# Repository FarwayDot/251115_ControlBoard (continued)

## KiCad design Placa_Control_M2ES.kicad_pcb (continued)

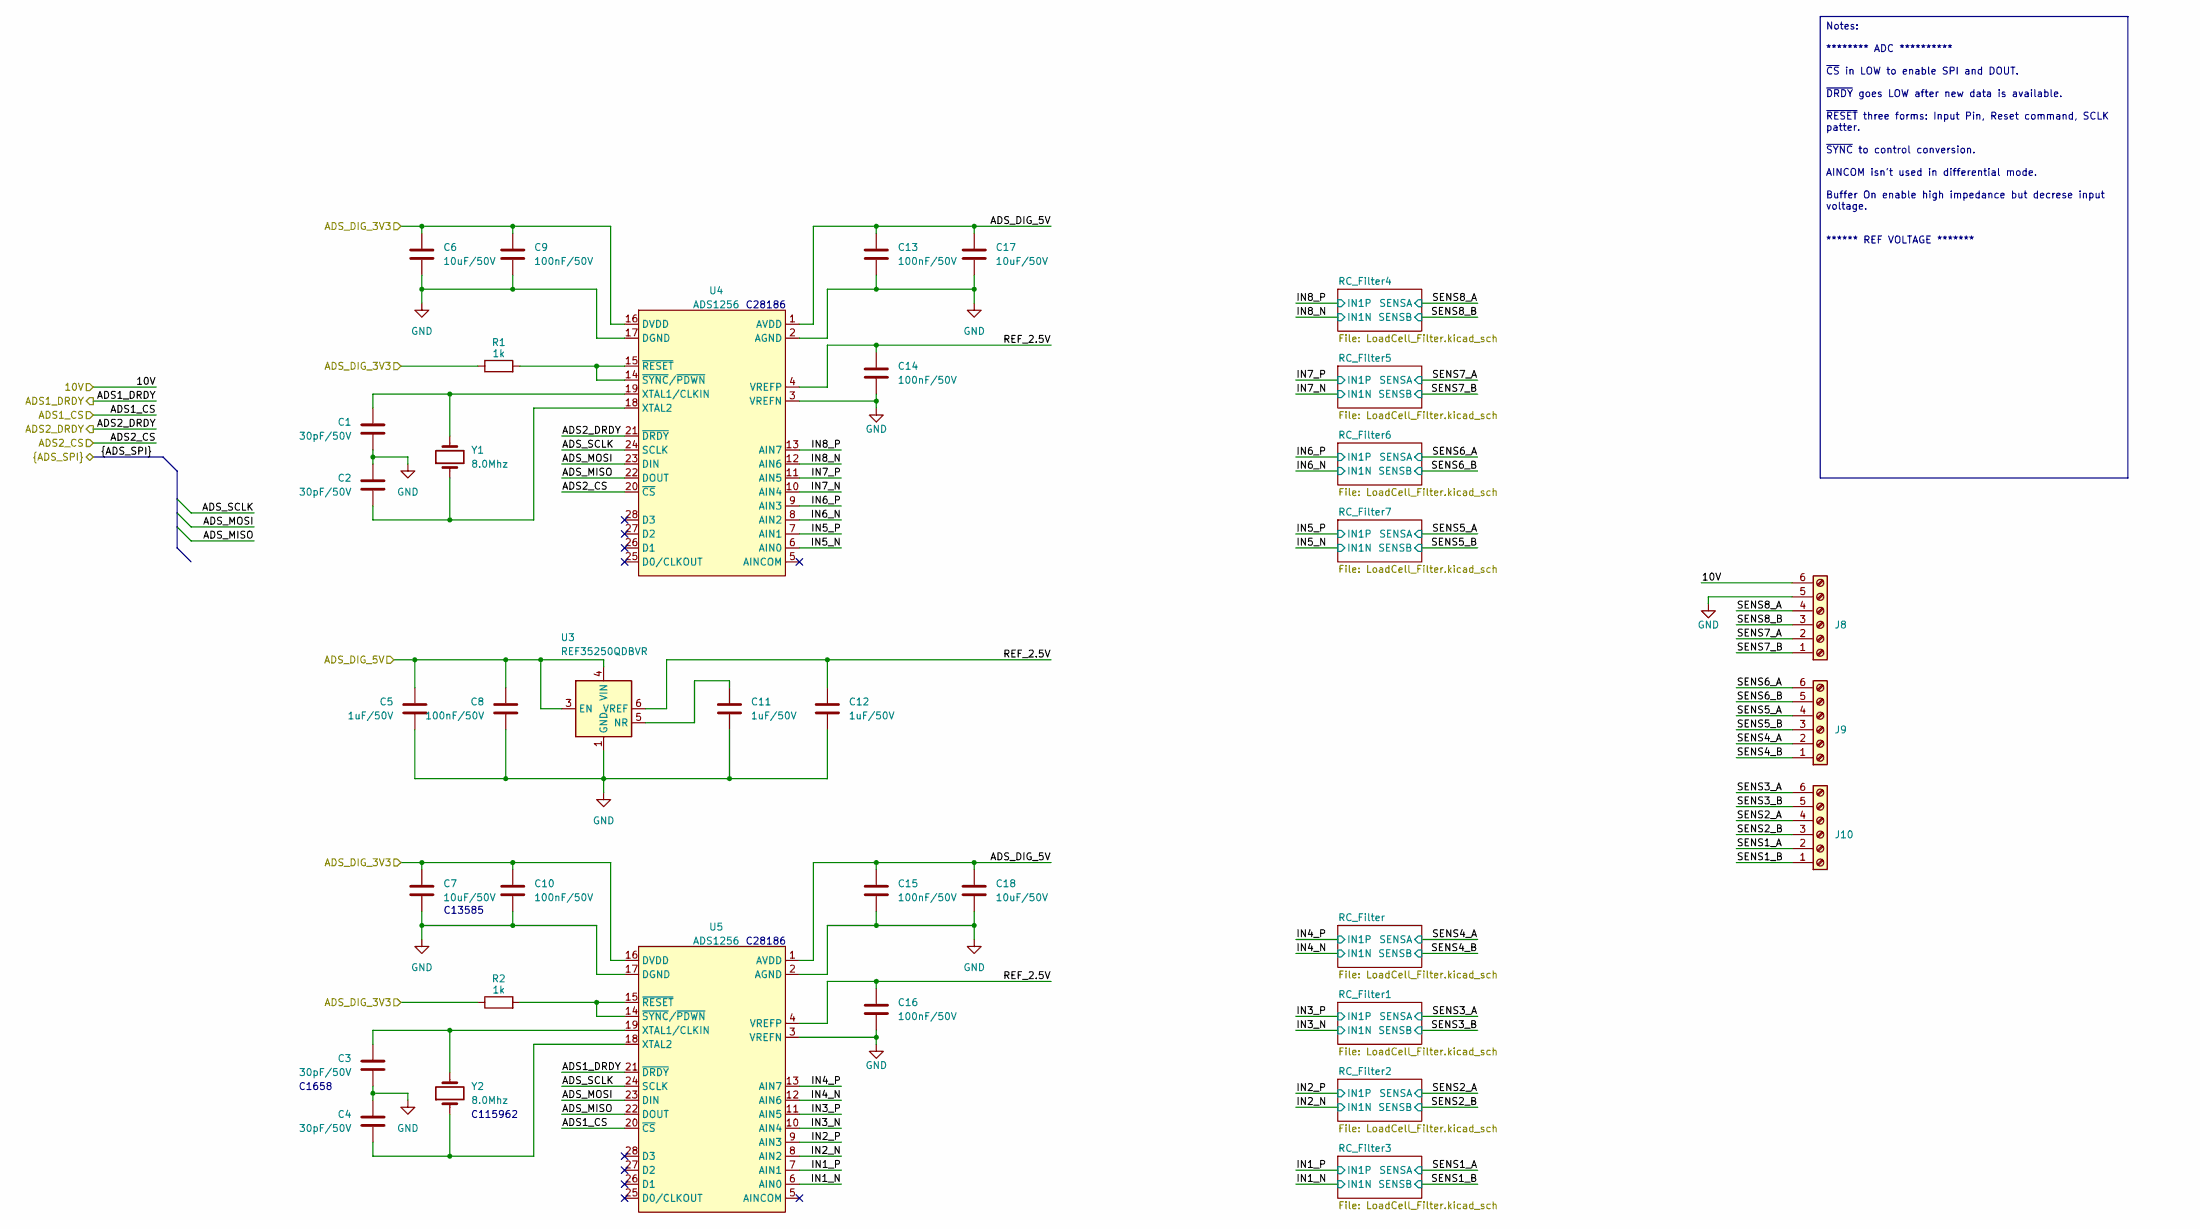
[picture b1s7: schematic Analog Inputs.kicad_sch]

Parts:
C1, C2, C3, C4: 30pF/50V; C_0603_1608Metric
C5, C11, C12: 1uF/50V; C_0805_2012Metric
C6, C7, C17, C18: 10uF/50V; C_1206_3216Metric
C8, C9, C10, C13, C14, C15, C16: 100nF/50V; C_0603_1608Metric
J8, J9, J10: Screw_Terminal_01x06; 15EDGVC_6P_3.81mm_Male-Vert_Degson
R1, R2: 1k; R_0603_1608Metric
U3: REF35250QDBVR; SOT-23-6
U4, U5: ADS1256; SSOP-28_5.3x10.2mm_P0.65mm
Y1, Y2: 8.0Mhz; Crystal_SMD_5032-2Pin_5.0x3.2mm

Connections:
/5V: C5.1, C8.1, C13.1, C15.1, C17.1, C18.1, U3.3 (EN), U3.4 (VIN), U4.1 (AVDD), U5.1 (AVDD); also elsewhere on the board
/10V: J8.6; also elsewhere on the board
/Analog Inputs/ADS1_CS: U5.20 (~CS); also elsewhere on the board
/Analog Inputs/ADS1_DRDY: U5.21 (~DRDY); also elsewhere on the board
/Analog Inputs/ADS2_CS: U4.20 (~CS); also elsewhere on the board
/Analog Inputs/ADS2_DRDY: U4.21 (~DRDY); also elsewhere on the board
/Analog Inputs/ADS_MISO: U4.22 (DOUT), U5.22 (DOUT); also elsewhere on the board
/Analog Inputs/ADS_MOSI: U4.23 (DIN), U5.23 (DIN); also elsewhere on the board
/Analog Inputs/ADS_SCLK: U4.24 (SCLK), U5.24 (SCLK); also elsewhere on the board
/Analog Inputs/IN1_N: U5.6 (AIN0); also elsewhere on the board
/Analog Inputs/IN2_N: U5.8 (AIN2); also elsewhere on the board
/Analog Inputs/IN2_P: U5.9 (AIN3); also elsewhere on the board
/Analog Inputs/IN3_N: U5.10 (AIN4); also elsewhere on the board
/Analog Inputs/IN3_P: U5.11 (AIN5); also elsewhere on the board
/Analog Inputs/IN4_N: U5.12 (AIN6); also elsewhere on the board
/Analog Inputs/IN4_P: U5.13 (AIN7); also elsewhere on the board
/Analog Inputs/IN5_N: U4.6 (AIN0); also elsewhere on the board
/Analog Inputs/IN5_P: U4.7 (AIN1); also elsewhere on the board
/Analog Inputs/IN6_N: U4.8 (AIN2); also elsewhere on the board
/Analog Inputs/IN6_P: U4.9 (AIN3); also elsewhere on the board
/Analog Inputs/IN7_N: U4.10 (AIN4); also elsewhere on the board
/Analog Inputs/IN7_P: U4.11 (AIN5); also elsewhere on the board
/Analog Inputs/IN8_N: U4.12 (AIN6); also elsewhere on the board
/Analog Inputs/IN8_P: U4.13 (AIN7); also elsewhere on the board
/Analog Inputs/REF_2.5V: C12.1, C14.1, C16.1, U3.6 (VREF), U4.4 (VREFP), U5.4 (VREFP)
/Analog Inputs/SENS1_A: J10.2; also elsewhere on the board
/Analog Inputs/SENS1_B: J10.1; also elsewhere on the board
/Analog Inputs/SENS2_A: J10.4; also elsewhere on the board
/Analog Inputs/SENS2_B: J10.3; also elsewhere on the board
/Analog Inputs/SENS3_A: J10.6; also elsewhere on the board
/Analog Inputs/SENS3_B: J10.5; also elsewhere on the board
/Analog Inputs/SENS4_A: J9.2; also elsewhere on the board
/Analog Inputs/SENS4_B: J9.1; also elsewhere on the board
/Analog Inputs/SENS5_A: J9.4; also elsewhere on the board
/Analog Inputs/SENS5_B: J9.3; also elsewhere on the board
/Analog Inputs/SENS6_A: J9.6; also elsewhere on the board
/Analog Inputs/SENS6_B: J9.5; also elsewhere on the board
/Analog Inputs/SENS7_A: J8.2; also elsewhere on the board
/Analog Inputs/SENS7_B: J8.1; also elsewhere on the board
/Analog Inputs/SENS8_A: J8.4; also elsewhere on the board
/Analog Inputs/SENS8_B: J8.3; also elsewhere on the board
GND: C1.2, C2.1, C3.2, C4.1, C5.2, C6.2, C7.2, C8.2, C9.2, C10.2, C11.2, C12.2, C13.2, C14.2, C15.2, C16.2, C17.2, C18.2, J8.5, U3.1 (GND), U3.2 (GND), U4.2 (AGND), U4.3 (VREFN), U4.17 (DGND), U5.2 (AGND), U5.3 (VREFN), U5.17 (DGND); also elsewhere on the board
unnamed: C11.1, U3.5 (NR)
unnamed: C1.1, U4.19 (XTAL1/CLKIN), Y1.2
unnamed: C2.2, U4.18 (XTAL2), Y1.1
unnamed: R1.2, U4.14 (~SYNC/~PDWN), U4.15 (~RESET)
unnamed: C3.1, U5.19 (XTAL1/CLKIN), Y2.2
unnamed: C4.2, U5.18 (XTAL2), Y2.1
unnamed: R2.2, U5.14 (~SYNC/~PDWN), U5.15 (~RESET)

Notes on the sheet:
C13585
C115962
C1658
C28186
Notes: ******** ADC ********** ~{CS} in LOW to enable SPI and DOUT. ~{DRDY} goes LOW after new data is available. ~{RESET} three forms: Input Pin, Reset command, SCLK patter. ~{SYNC} to control conversion. AINCOM isn't used in differential mode. Buffer On enable high impedance but decrese input vol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

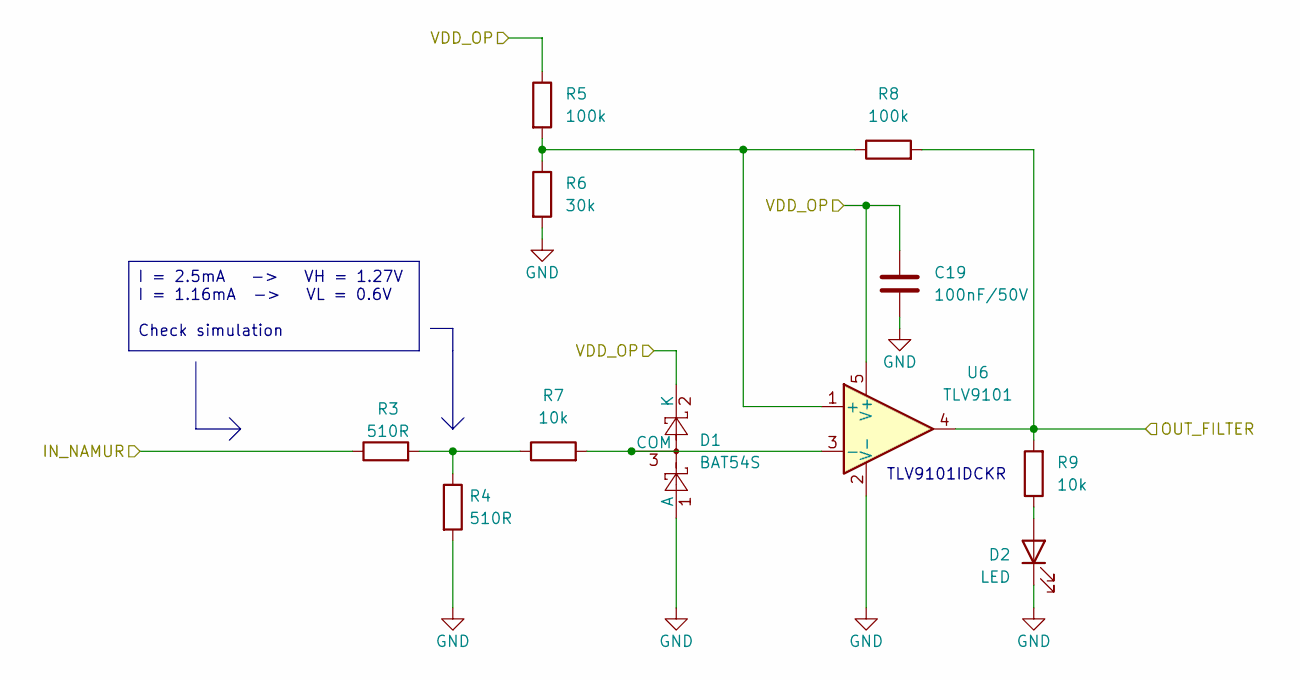
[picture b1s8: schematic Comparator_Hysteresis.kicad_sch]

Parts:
C19: 100nF/50V; C_0603_1608Metric
D1: BAT54S; SOT-23
D2: LED; LED_0805_2012Metric
R3, R4: 510R; R_0603_1608Metric
R5, R8: 100k; R_0603_1608Metric
R6: 30k; R_0603_1608Metric
R7, R9: 10k; R_0603_1608Metric
U6: TLV9101; SC70-5_TexasInstruments

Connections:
/Digital Inputs/DIG_2: R8.2, R9.2, U6.4; also elsewhere on the board
/Digital Inputs/NAMUR_2: R3.1; also elsewhere on the board
GND: C19.2, D1.1 (A), D2.1 (K), R4.2, R6.2, U6.2 (V-); also elsewhere on the board
unnamed: D1.3 (COM), R7.2, U6.3 (-)
unnamed: D2.2 (A), R9.1
unnamed: R3.2, R4.1, R7.1
unnamed: R5.2, R6.1, R8.1, U6.1 (+)

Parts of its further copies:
C66, C67, C68, C69, C70, C71, C72, C73: 100nF/50V; C_0603_1608Metric
D3, D5, D7, D9, D11, D13, D15, D17: BAT54S; SOT-23
D4, D6, D8, D10, D12, D14, D16, D18: LED; LED_0805_2012Metric
R60, R61, R67, R68, R74, R75, R81, R82, R88, R89, R95, R96, R102, R103, R109, R110: 510R; R_0603_1608Metric
R62, R65, R69, R72, R76, R79, R83, R86, R90, R93, R97, R100, R104, R107, R111, R114: 100k; R_0603_1608Metric
R63, R70, R77, R84, R91, R98, R105, R112: 30k; R_0603_1608Metric
R64, R66, R71, R73, R78, R80, R85, R87, R92, R94, R99, R101, R106, R108, R113, R115: 10k; R_0603_1608Metric
U14, U15, U16, U17, U18, U19, U20, U21: TLV9101; SC70-5_TexasInstruments

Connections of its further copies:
/Digital Inputs/DIG_1: R65.2, R66.2, U14.4; also elsewhere on the board
/Digital Inputs/DIG_3: R72.2, R73.2, U15.4; also elsewhere on the board
/Digital Inputs/DIG_4: R79.2, R80.2, U16.4; also elsewhere on the board
/Digital Inputs/DIG_5: R86.2, R87.2, U17.4; also elsewhere on the board
/Digital Inputs/DIG_6: R93.2, R94.2, U18.4; also elsewhere on the board
/Digital Inputs/DIG_7: R100.2, R101.2, U19.4; also elsewhere on the board
/Digital Inputs/DIG_8: R107.2, R108.2, U20.4; also elsewhere on the board
/Digital Inputs/DIG_9: R114.2, R115.2, U21.4; also elsewhere on the board
/Digital Inputs/NAMUR_1: R60.1; also elsewhere on the board
/Digital Inputs/NAMUR_3: R67.1; also elsewhere on the board
/Digital Inputs/NAMUR_4: R74.1; also elsewhere on the board
/Digital Inputs/NAMUR_5: R81.1; also elsewhere on the board
/Digital Inputs/NAMUR_6: R88.1; also elsewhere on the board
/Digital Inputs/NAMUR_7: R95.1; also elsewhere on the board
/Digital Inputs/NAMUR_8: R102.1; also elsewhere on the board
/Digital Inputs/NAMUR_9: R109.1; also elsewhere on the board
GND: C66.2, C67.2, C68.2, C69.2, C70.2, C71.2, C72.2, C73.2, D3.1 (A), D4.1 (K), D5.1 (A), D6.1 (K), D7.1 (A), D8.1 (K), D9.1 (A), D10.1 (K), D11.1 (A), D12.1 (K), D13.1 (A), D14.1 (K), D15.1 (A), D16.1 (K), D17.1 (A), D18.1 (K), R61.2, R63.2, R68.2, R70.2, R75.2, R77.2, R82.2, R84.2, R89.2, R91.2, R96.2, R98.2, R103.2, R105.2, R110.2, R112.2, U14.2 (V-), U15.2 (V-), U16.2 (V-), U17.2 (V-), U18.2 (V-), U19.2 (V-), U20.2 (V-), U21.2 (V-); also elsewhere on the board
unnamed: D3.3 (COM), R64.2, U14.3 (-)
unnamed: D4.2 (A), R66.1
unnamed: D5.3 (COM), R71.2, U15.3 (-)
unnamed: D6.2 (A), R73.1
unnamed: D7.3 (COM), R78.2, U16.3 (-)
unnamed: D8.2 (A), R80.1
unnamed: D9.3 (COM), R85.2, U17.3 (-)
unnamed: D10.2 (A), R87.1
unnamed: D11.3 (COM), R92.2, U18.3 (-)
unnamed: D12.2 (A), R94.1
unnamed: D13.3 (COM), R99.2, U19.3 (-)
unnamed: D14.2 (A), R101.1
unnamed: D15.3 (COM), R106.2, U20.3 (-)
unnamed: D16.2 (A), R108.1
unnamed: D17.3 (COM), R113.2, U21.3 (-)
unnamed: D18.2 (A), R115.1
unnamed: R60.2, R61.1, R64.1
unnamed: R67.2, R68.1, R71.1
unnamed: R74.2, R75.1, R78.1
unnamed: R81.2, R82.1, R85.1
unnamed: R88.2, R89.1, R92.1
unnamed: R95.2, R96.1, R99.1
unnamed: R102.2, R103.1, R106.1
unnamed: R109.2, R110.1, R113.1
unnamed: R62.2, R63.1, R65.1, U14.1 (+)
unnamed: R69.2, R70.1, R72.1, U15.1 (+)
unnamed: R76.2, R77.1, R79.1, U16.1 (+)
unnamed: R83.2, R84.1, R86.1, U17.1 (+)
unnamed: R90.2, R91.1, R93.1, U18.1 (+)
unnamed: R97.2, R98.1, R100.1, U19.1 (+)
unnamed: R104.2, R105.1, R107.1, U20.1 (+)
unnamed: R111.2, R112.1, R114.1, U21.1 (+)

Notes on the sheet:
TLV9101IDCKR
I = 2.5mA -> VH = 1.27V I = 1.16mA -> VL = 0.6V Check simulation

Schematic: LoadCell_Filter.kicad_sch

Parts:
C31: 10nF/50V; C_0603_1608Metric
C32, C33: 1nF/50V; C_0603_1608Metric
R10, R11, R12, R13: 10k; R_0603_1608Metric

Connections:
/Analog Inputs/IN4_N: C31.2, C33.2, R11.2, R13.1; also elsewhere on the board
/Analog Inputs/IN4_P: C31.1, C32.1, R10.1, R12.1; also elsewhere on the board
/Analog Inputs/SENS4_A: R12.2; also elsewhere on the board
/Analog Inputs/SENS4_B: R13.2; also elsewhere on the board
GND: C32.2, C33.1, R10.2, R11.1; also elsewhere on the board

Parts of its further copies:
C34, C37, C40, C43, C46, C49, C63: 10nF/50V; C_0603_1608Metric
C35, C36, C38, C39, C41, C42, C44, C45, C47, C48, C50, C51, C64, C65: 1nF/50V; C_0603_1608Metric
R14, R15, R16, R17, R18, R19, R20, R21, R22, R23, R24, R25, R26, R27, R28, R29, R30, R31, R32, R33, R34, R35, R36, R37, R56, R57, R58, R59: 10k; R_0603_1608Metric

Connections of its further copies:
/Analog Inputs/IN1_N: C40.2, C42.2, R23.2, R25.1; also elsewhere on the board
/Analog Inputs/IN2_N: C34.2, C36.2, R15.2, R17.1; also elsewhere on the board
/Analog Inputs/IN2_P: C34.1, C35.1, R14.1, R16.1; also elsewhere on the board
/Analog Inputs/IN3_N: C37.2, C39.2, R19.2, R21.1; also elsewhere on the board
/Analog Inputs/IN3_P: C37.1, C38.1, R18.1, R20.1; also elsewhere on the board
/Analog Inputs/IN5_N: C63.2, C65.2, R57.2, R59.1; also elsewhere on the board
/Analog Inputs/IN5_P: C63.1, C64.1, R56.1, R58.1; also elsewhere on the board
/Analog Inputs/IN6_N: C49.2, C51.2, R35.2, R37.1; also elsewhere on the board
/Analog Inputs/IN6_P: C49.1, C50.1, R34.1, R36.1; also elsewhere on the board
/Analog Inputs/IN7_N: C46.2, C48.2, R31.2, R33.1; also elsewhere on the board
/Analog Inputs/IN7_P: C46.1, C47.1, R30.1, R32.1; also elsewhere on the board
/Analog Inputs/IN8_N: C43.2, C45.2, R27.2, R29.1; also elsewhere on the board
/Analog Inputs/IN8_P: C43.1, C44.1, R26.1, R28.1; also elsewhere on the board
/Analog Inputs/SENS1_A: R24.2; also elsewhere on the board
/Analog Inputs/SENS1_B: R25.2; also elsewhere on the board
/Analog Inputs/SENS2_A: R16.2; also elsewhere on the board
/Analog Inputs/SENS2_B: R17.2; also elsewhere on the board
/Analog Inputs/SENS3_A: R20.2; also elsewhere on the board
/Analog Inputs/SENS3_B: R21.2; also elsewhere on the board
/Analog Inputs/SENS5_A: R58.2; also elsewhere on the board
/Analog Inputs/SENS5_B: R59.2; also elsewhere on the board
/Analog Inputs/SENS6_A: R36.2; also elsewhere on the board
/Analog Inputs/SENS6_B: R37.2; also elsewhere on the board
/Analog Inputs/SENS7_A: R32.2; also elsewhere on the board
/Analog Inputs/SENS7_B: R33.2; also elsewhere on the board
/Analog Inputs/SENS8_A: R28.2; also elsewhere on the board
/Analog Inputs/SENS8_B: R29.2; also elsewhere on the board
GND: C35.2, C36.1, C38.2, C39.1, C41.2, C42.1, C44.2, C45.1, C47.2, C48.1, C50.2, C51.1, C64.2, C65.1, R14.2, R15.1, R18.2, R19.1, R22.2, R23.1, R26.2, R27.1, R30.2, R31.1, R34.2, R35.1, R56.2, R57.1; also elsewhere on the board

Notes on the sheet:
To ADC
From Sensor
Notes: - Use Precision Resistor - Fc = 1500Hz (simulated)

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
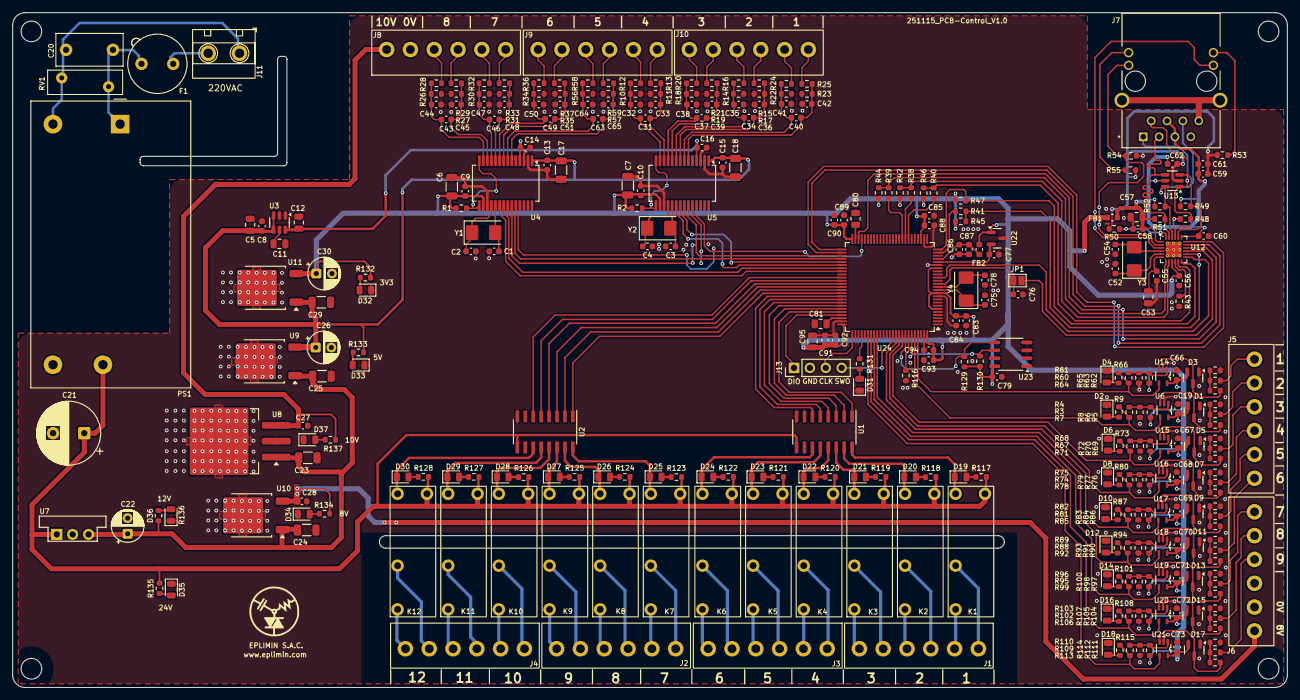
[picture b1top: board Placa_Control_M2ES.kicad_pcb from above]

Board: 2 copper layers, 204.0 x 108.0 mm, 326 parts (0 on the bottom side), 221 nets.

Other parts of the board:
G1: LOGO

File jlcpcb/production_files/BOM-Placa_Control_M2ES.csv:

Comment,Designator,Footprint,LCSC,Quantity
450mR/200mA,"FB1,FB2",L_0603_1608Metric,C1002,2
USBLC6-4SC6,U13,SOT-23-6,C111212,1
25Mhz,Y3,Crystal_SMD_5032-2Pin_5.0x3.2mm,C112569,1
8.0Mhz,"Y1,Y2,Y4",Crystal_SMD_5032-2Pin_5.0x3.2mm,C115962,3
uA7810,U8,TO-263-3_TabPin2,C131966,1
10uF/50V,"C17,C18,C6,C7",C_1206_3216Metric,C13585,4
100nF/50V,"C10,C13,C14,C15,C16,C19,C27,C28,C56,C58,C59,C60,C61,C62,C66,C67,C68,C69,C70,C71,C72,C73,C76,C77,C79,C8,C83,C85,C87,C89,C9,C91,C93",C_0603_1608Metric,C14663,33
24xx256,U23,SO-8_3.9x4.9mm_P1.27mm,C152172,1
LD29150DT33R,U11,TO-252-2,C155674,1
LD29150DT50R,U9,TO-252-2,C157411,1
L78M08CDT-TR,U10,TO-252-2,C158076,1
1nF/50V,"C32,C33,C35,C36,C38,C39,C41,C42,C44,C45,C47,C48,C50,C51,C64,C65",C_0603_1608Metric,C1588,16
30pF/50V,"C1,C2,C3,C4,C52,C54,C75,C78",C_0603_1608Metric,C1658,8
1uF/50V,"C23,C24,C25,C29",C_1206_3216Metric,C1848,4
1k,"R1,R116,R2,R47",R_0603_1608Metric,C21190,4
12k1,R50,R_0603_1608Metric,C22864,1
30k,"R105,R112,R6,R63,R70,R77,R84,R91,R98",R_0603_1608Metric,C22984,9
33R,"R38,R39,R40,R41",R_0603_1608Metric,C23140,4
49R9,"R48,R49,R51,R52",R_0603_1608Metric,C23185,4
5k1,"R131,R132,R133,R134",R_0603_1608Metric,C23186,4
510R,"R102,R103,R109,R110,R3,R4,R60,R61,R67,R68,R74,R75,R81,R82,R88,R89,R95,R96",R_0603_1608Metric,C23193,18
100k,"R100,R104,R107,R111,R114,R5,R62,R65,R69,R72,R76,R79,R8,R83,R86,R90,R93,R97",R_0603_1608Metric,C25803,18
10k,"R10,R101,R106,R108,R11,R113,R115,R117,R118,R119,R12,R120,R121,R122,R123,R124,R125,R126,R127,R128,R13,R135,R136,R137,R14,R15,R16,R17,R18,R19,R20,R21,R22,R23,R24,R25,R26,R27,R28,R29,R30,R31,R32,R33,R34,R35,R36,R37,R42,R43,R44,R45,R46,R53,R54,R55,R56,R57,R58,R59,R64,R66,R7,R71,R73,R78,R80,R85,R87,R9,R92,R94,R99",R_0603_1608Metric,C25804,73
ADS1256,"U4,U5",SSOP-28_5.3x10.2mm_P0.65mm,C28186,2
1uF/50V,"C11,C12,C5,C53,C57",C_0805_2012Metric,C28323,5
STM32F407VGTx,U24,LQFP-100_14x14mm_P0.5mm,C28730,1
2u2F/50V,"C80,C81,C95",C_0805_2012Metric,C377773,3
REF3030,U22,SOT-23,C38423,1
2k2,"R129,R130",R_0603_1608Metric,C4190,2
TLV9101,"U14,U15,U16,U17,U18,U19,U20,U21,U6",SC70-5_TexasInstruments,C4367797,9
10nF/50V,"C31,C34,C37,C40,C43,C46,C49,C55,C63,C84,C86,C88,C90,C92,C94",C_0603_1608Metric,C57112,15
LAN8742A,U12,VQFN-24-1EP_4x4mm_P0.5mm_EP2.5x2.5mm_ThermalVias,C621425,1
REF35250QDBVR,U3,SOT-23-6,C6265005,1
BAT54S,"D1,D11,D13,D15,D17,D3,D5,D7,D9",SOT-23,C7420333,9
ULN2003,"U1,U2",SOIC-16_3.9x9.9mm_P1.27mm,C7512,2
LED,"D10,D12,D14,D16,D18,D19,D2,D20,D21,D22,D23,D24,D25,D26,D27,D28,D29,D30,D31,D32,D33,D34,D35,D36,D37,D4,D6,D8",LED_0805_2012Metric,C84256,28
Screw_Terminal_01x06,J6,15EDGVC_6P_3.81mm_Male-Vert_Degson,,1
Screw_Terminal_01x06,J9,15EDGVC_6P_3.81mm_Male-Vert_Degson,,1
Screw_Terminal_01x06,J5,15EDGVC_6P_3.81mm_Male-Vert_Degson,,1
HF46F-G,K1,Relay_HF46F-G_Hongfa,,1
Screw_Terminal_01x06,J4,15EDGVC_6P_3.81mm_Male-Vert_Degson,,1
Jumper_2_Bridged,JP1,SolderJumper-2_P1.3mm_Open_Pad1.0x1.5mm,,1
10uF/25V,C30,CP_Radial_D5.0mm_P2.50mm,,1
HF46F-G,K6,Relay_HF46F-G_Hongfa,,1
HF46F-G,K4,Relay_HF46F-G_Hongfa,,1
HF46F-G,K5,Relay_HF46F-G_Hongfa,,1
HF46F-G,K3,Relay_HF46F-G_Hongfa,,1
250VAC 0.5AAC,F1,Fuseholder_TR5_Littelfuse_No560_No460,,1
HF46F-G,K10,Relay_HF46F-G_Hongfa,,1
HF46F-G,K2,Relay_HF46F-G_Hongfa,,1
Screw_Terminal_01x04,J13,PinHeader_1x04_P2.54mm_Vertical,,1
Screw_Terminal_01x06,J1,15EDGVC_6P_3.81mm_Male-Vert_Degson,,1
ARJM11C7-009-AB-EW2,J7,ARJM11C7-009-AB-EW2_Abracon,,1
HF46F-G,K7,Relay_HF46F-G_Hongfa,,1
10D561K,RV1,RV_Disc_D12mm_W3.9mm_P7.5mm,,1
Screw_Terminal_01x06,J3,15EDGVC_6P_3.81mm_Male-Vert_Degson,,1
Screw_Terminal_01x06,J8,15EDGVC_6P_3.81mm_Male-Vert_Degson,,1
10uF/25V,C22,CP_Radial_D5.0mm_P2.50mm,,1
10uF/25V,C26,CP_Radial_D5.0mm_P2.50mm,,1
IRM-10-24,PS1,Converter_ACDC_MeanWell_IRM-10-xx_THT,,1
Screw_Terminal_01x06,J10,15EDGVC_6P_3.81mm_Male-Vert_Degson,,1
100nF/400VAC,C20,C_Disc_D10.5mm_W5.0mm_P7.50mm,,1
HF46F-G,K11,Relay_HF46F-G_Hongfa,,1
HF46F-G,K12,Relay_HF46F-G_Hongfa,,1
100uF/50v,C21,CP_Radial_D10.0mm_P5.00mm,,1
Screw_Terminal_01x06,J2,15EDGVC_6P_3.81mm_Male-Vert_Degson,,1
OKI-78SR-12_1.0-W36-C,U7,Converter_DCDC_Murata_OKI-78SR_Vertical,,1
Screw_Terminal_01x02,J11,DG126_5.0_02P,,1
HF46F-G,K8,Relay_HF46F-G_Hongfa,,1
HF46F-G,K9,Relay_HF46F-G_Hongfa,,1

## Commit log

2025-11-15 Primer Commit
2025-11-17 Avance con el ADC para conectar al filtro para las celdas. Se debe realizar un excel para el cálculo del peso y cuadrar bien esa sección para que la programación sea lo más sencilla posible
2025-11-18 Se culmina en que se utilizarà un filtro a 1.5khz para el sensor con divisor de 10k para la entrada ananaloga para el adc externo
2025-11-19 Se termina el circuito de entrada análoga, se escoge la bornera. Se termina las salidas de rele, se asumen que se trabajara maximo a 220V y solo para activar contactores. El circuito para el sensor n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
2025-11-20 Avance
2025-11-21 avance de pcb, se considera borneras externas para conexión de alimentación
2025-11-22 Avance del posicionamiento
2025-11-24 Se empieza a evaluar la conexión del ethernet con la carcasa, parte analog, dig y micro en posición, tambien se busca solución para la salida de led de las entradas digitales
2025-11-25 Se traza vcc, digital, analog, relay, esta por terminar corregir GND y revisar nuevamente
2025-11-26 Se termina de revisar la placa. Se corrige la terminación de los transformadores internos del puerto ethernet. Se revisa GND, espaciado, añadimos notas. Falta enlazar las partes de JLCPCN
2025-11-26 Se revisa informacion del ruteo para ethernet, los trazos MII y MDI pueden estar con un plano de GND adyacente. Lo que no puede tener acoplamiento es la parte magnética.
2025-11-26 Se crea nueva version debido a que el anterior diseño estaba para un uC stm32h7. Este nuevo diseño corresponde al stm32f407v utilizado en el esterilizador y otros proyectos conocidos en la empresa.
2025-11-27 Se corrige el nombre para la ref de 2.5V para los canales análogos, Se corrigen quita un capacitor en cada pin VCAP, Se actualiza PCB
2025-11-28 Se añaden leds a la entrada de los Namur. Se estandariza y revisan varios footprints de los capacitores. El cambio no fue demasiado, se corrigio en placa. Se hacen algunos cambios adicionales a los v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
2025-12-04 Se añade led de status y eeprom externa. Se actualiza pcb y se añade serigrafía adicional. Se actualiza los componentes jlcpcb, se utiliza un micro con con 512kbytes de flash a recomendacion de jefry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
2026-03-10 Se añade la carpeta Docs y se guarda el schematico y vista 3d para conexiones
